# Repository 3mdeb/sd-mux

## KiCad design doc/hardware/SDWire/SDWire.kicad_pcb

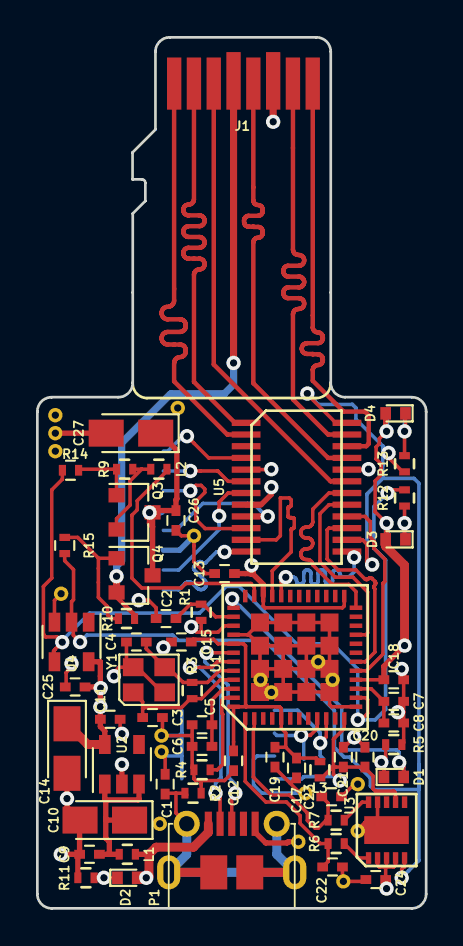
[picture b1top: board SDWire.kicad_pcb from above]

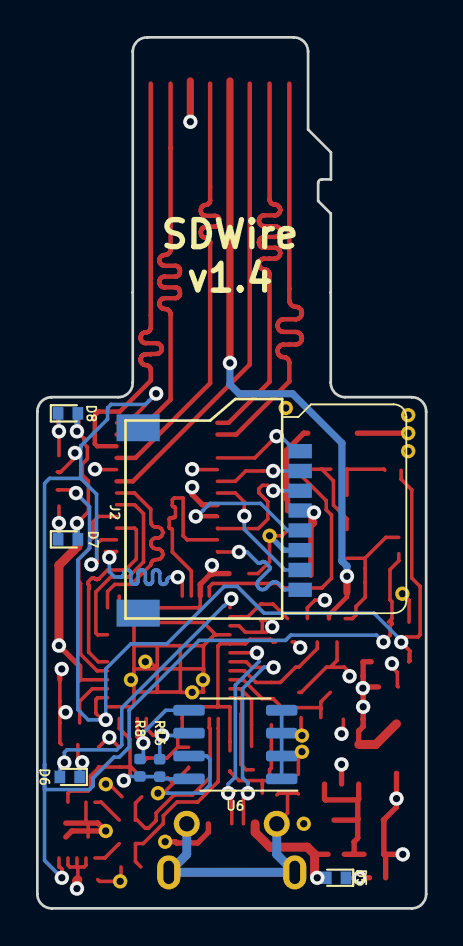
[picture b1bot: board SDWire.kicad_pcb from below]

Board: 4 copper layers, 21.6 x 48.4 mm, 65 parts (8 on the bottom side), 51 nets.

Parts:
C1, C2, C6, C8, C9, C11, C12, C13, C15, C17, C18, C20, C24, C25, C26: 100nF/16V; C_0402
C3, C4: 33p/50V; C_0402
C5, C7, C19, C21: 1uF/16V; C_0402
C10, C14, C27: 10uF/10V; CP_Tantalum_Case-A_EIA-3216-18_Reflow
C22, C23: 47pF; C_0402
D1: OSB50402C1E; LED_0402
D2, D5: RED; LED_0402
D3, D6, D7: BLUE; LED_0402
D4, D8: GREEN; LED_0402
J1: usd-plug; usd
J2: uSD Socket; usd-attend
L1, L2, L3: BLM15PD121SN1D; R_0402
P1: USB_OTG_MICRO_USB; micro_sub_molex
Q3, Q4: MMBT4403LT1; SOT-23
R1, R2, R9, R10: 10K; R_0402
R3: 1M; R_0402
R4: 12k 1%; R_0402
R5: 330R; R_0402
R6, R7: 27R; R_0402
R8, R16: 10K; R_0402_1005Metric
R11, R12, R13, R14, R15: 1K; R_0402
U1: USB2640-HZH-02; QFN-48-1EP_7x7mm_Pitch0.5mm
U2: SPX3819M5; SOT-23-5
U3: FT200XD; DFN-10-1EP_3x3mm_Pitch0.5mm
U4: MC74HC1G04DTT1G; SOT-23-5
U5: TS3A27518EPWR; TSSOP-24
U6: AT24CS02-SSHM; SO-8_3.9x4.9mm_P1.27mm
Y1: 24MHz; Crystal_SMD_2520-4pin_2.5x2.0mm

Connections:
+3V3: C11.1, C13.1, C14.1, C18.1, C20.1, C21.1, C24.1, C25.1, D3.2, D4.2, D7.2, D8.2, L3.1, R1.1, R8.1, R16.1, U1.12, U1.16, U1.25, U1.34, U1.39, U2.5, U3.2, U3.3, U3.4, U3.7, U4.5, U5.8, U6.8
/CLK_DUT: J1.5, U5.21
/CLK_TS: U1.21, U5.17
/CMD_DUT: J1.3, U5.19
/CMD_TS: U1.24, U5.18
/DAT0_DUT: J1.7, U5.23
/DAT0_TS: U1.18, U5.15
/DAT1_DUT: J1.8, U5.22
/DAT1_TS: U1.17, U5.16
/DAT2_DUT: J1.1, U5.2
/DAT2_TS: U1.33, U5.11
/DAT3_DUT: J1.2, U5.1
/DAT3_TS: U1.32, U5.13
/SOCKET_SEL: R13.2, R15.2, U3.5, U4.2, U5.14, U5.24
/USB_B+: C23.1, R7.2, U1.2
/USB_B-: C22.1, R6.2, U1.1
/USB_UP+: P1.3, U1.42
/USB_UP-: P1.2, U1.43
/USD_VDD: C26.1, C27.1, J2.4, Q3.3, Q4.3
/VDD: D2.2, D5.2, L1.2, P1.1
/VDD_DUT: J1.4, Q4.2, R10.2
/VDD_TS: L2.1, Q3.2, R9.2
/~CD_TS: R12.2, R14.2, U1.14, U4.4
/~RESET: C2.1, R1.2, U1.38
GND: C1.2, C2.2, C3.2, C4.2, C5.2, C6.2, C7.2, C8.2, C9.2, C10.2, C11.2, C12.2, C13.2, C14.2, C15.2, C17.2, C18.2, C19.2, C20.2, C21.2, C22.2, C23.2, C24.2, C25.2, C26.2, C27.2, J1.6, J2.6, P1.5, R2.2, R4.2, R5.2, R11.2, U1.13, U1.40, U1.49, U2.2, U3.9, U3.11, U4.3, U5.5, U5.20, U6.1, U6.2, U6.3, U6.4, U6.7, Y1.2, Y1.4
unnamed: C1.1, P1.6, R2.1
unnamed: C3.1, R3.2, U1.45, Y1.1
unnamed: C4.1, R3.1, U1.44, Y1.3
unnamed: C5.1, C6.1, U1.46
unnamed: C7.1, C8.1, U1.15
unnamed: C9.1, C10.1, L1.1, U2.1, U2.3
unnamed: C12.1, C15.1, C17.1, C19.1, L3.2, U1.5, U1.41, U1.48
unnamed: D1.1, D6.1, R5.1
unnamed: D1.2, D6.2, U1.37
unnamed: D2.1, D5.1, R11.1
unnamed: D3.1, D7.1, R12.1
unnamed: D4.1, D8.1, R13.1
unnamed: J2.1, U5.4
unnamed: J2.2, U5.6
unnamed: J2.3, U5.10
unnamed: J2.5, U5.9
unnamed: J2.7, U5.7
unnamed: J2.8, U5.12
unnamed: L2.2, U1.35
unnamed: Q3.1, R9.1, R14.1
unnamed: Q4.1, R10.1, R15.1
unnamed: R4.1, U1.47
unnamed: R6.1, U3.1
unnamed: R7.1, U3.10
unnamed: R8.2, U1.10, U6.5
unnamed: R16.2, U1.9, U6.6

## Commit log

2017-07-18 Add PRODUCT ID option to command line interface
    This change introduces possiblity of using FTDI devices
    other than FT245RL.
2017-07-18 Add device type setting in --set-serial function
    This setting is needed to distinguish one type of FTDI chip
    from another.
2017-10-23 Introduce device type and make the code use of it
    NOTE: this patch needs extra functionality of libftdi1 library.
    The functionality is ftdi_eeprom_get_strings(). It is available
    in libftdi1 since 1.4rc1 version.
2017-10-23 Introduce device features and make use of them
    Device features are used to check whether given functionality is
    available on given board or not.
2017-10-23 Implement SDWire specific SD MUX controller
2018-03-21 Require libftdi1 version 1.4 or newer
    Version 1.4 is the first to support ftdi_eeprom_get_strings() function.
2018-06-13 Lengthen micro SD card adapter
    The lengthening had to be done mainly because of boards housings.
    Usually, walls of the housing caused prolems with inserting adapter
    into their card socket. Now the adaper is 5mm longer.
2018-06-13 Add fabrication files for micro SD card adapter v2
2018-06-13 Add hardware documentation of SDWire device
2018-06-13 Add fabrication and assembly files
    Fabrication files are for a PCB manufacturer and assembly files are for an assembler.
2019-01-08 Add support for USB-MUX device
2019-05-20 Add EEPROM to SDWire device
    EEPROM is used to store unique serial number for mass storage
    reader in order to distinguish them in one USB host machine.
2019-05-20 create group sd-mux-ctrl
    Let the Debian package installer create a new group sd-mux-ctrl. Give the
    group access to the SD-MUX devices via a udev rule.
2019-05-20 sd-mux-ctrl.1: fix title
    Debian installs the man page under man2 due to an incorrect title line.
    man man-pages indicates how the title line should be formatted.
    Provide a corrected title line.
2019-05-20 setSerial: do not use default device type
    When setting the serial number with the wrong device type the SD-Wire
    device becomes unusable until the serial number is set again specifying the
    correct device type. So using 'sd-mux' as default device type is unwise.
    Let's require that a device type is specified when executing the set serial
    command.
2019-05-20 parseArguments: avoid segmentation fault
    If an incorrect command line argument is provided poptBadOption() is
    called. Freeing the context optCon before this call leads to a
    segmentation fault.
    If no command line argument is provided we should free the context after
    displaying the usage information to avoid a memory leak.
2019-05-20 debian/control: missing build dependencies
    Building with pbuilder highlights the following missing build dependencies:
    - cmake
    - pkg-config
    Add the missing build dependencies. Reformat dependencies.
2019-05-20 parseArguments(): use correct data type
    Compilation on arm64 with gcc (Debian 8.2.0-21) 8.2.0 results in errors:
    src/main.cpp: In function ‘int parseArguments(...)’:
    src/main.cpp:711:41: error: comparison is always true due to limited range
    of data type [-Werror=type-limits]
    while ((c = poptGetNextOpt(optCon)) >= 0) {
    ~~~~~~~~~~~~~~~~~~~~~~~~~~~~~^~~~
2019-05-20 Add file debian/source/format
    The `Debian New Maintainers' Guide` specifies in
    https://www.debian.org/doc/manuals/maint-guide/dother.en.html#sourcef
    that each Debian package should have a file debian/source/format.
    `3.0 (native)` is the format to specify when quilt is not used.
    Remove misplaced file debian/format.
2019-05-20 doc/man: fix typo
    %s/untill/until/
2019-05-21 Update Standards-Version in debian packaging
2019-09-09 Update assembly layer
2019-09-09 Add fabrication and assembly documentation
2020-02-17 Increase power off time for USB device
    USB SSD drives seem to have big enough capacitors to
    keep them powered for more than 100ms. This change
    increase the power off time to 500ms to let them discharge
    and reset the drive properly.

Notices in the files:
doc/hardware/SDWire/SDWire.kicad_pcb:
Copyright (c) 2016 Samsung Electronics Co., Ltd All Rights Reserved
